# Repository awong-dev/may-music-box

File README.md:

# May Music Box

This is a little project I made for my daughter. It's an
mp3 player that reads off an SD-card that's built to
replace the guts of a Munchkin Mozart Music Cube.

Why do this? Cause electronic beepy toys for toddlers
are sooo much better if you can control what gets played
on them. :)

## Features
  * Super low power draw. Inactive, draws around 210uA. Active ~50-60mA. With a 1200mAH battery, that's ~8 months of sleep (not really since the battery will leak), or 20 hours of play on one charge.
  * Hardware button debounce. Cuz I could.
  * LEDs that act ike Peak-meter to give your toddler the authentic club feel.
  * Way too much love and sweat put into buliding this thing.
  * The word "mayberry" is printed on the PCB. :)

## What's in this repository
  * Arduino sketch for the MCU that handles the input buttons and playback.
  * vdsp4 assembly code for handling mono downmix, and LED pulsing in of the VS1053b chip
  * Eagle files for the contol PCB.

## Quirks
  * There is a fork of the Adafruit vs1053b library. The mainline library has (multiple) synchronization bugs that lead to corrupted state. This fork fixes the major ones. Remove once upstream merges the fixes.

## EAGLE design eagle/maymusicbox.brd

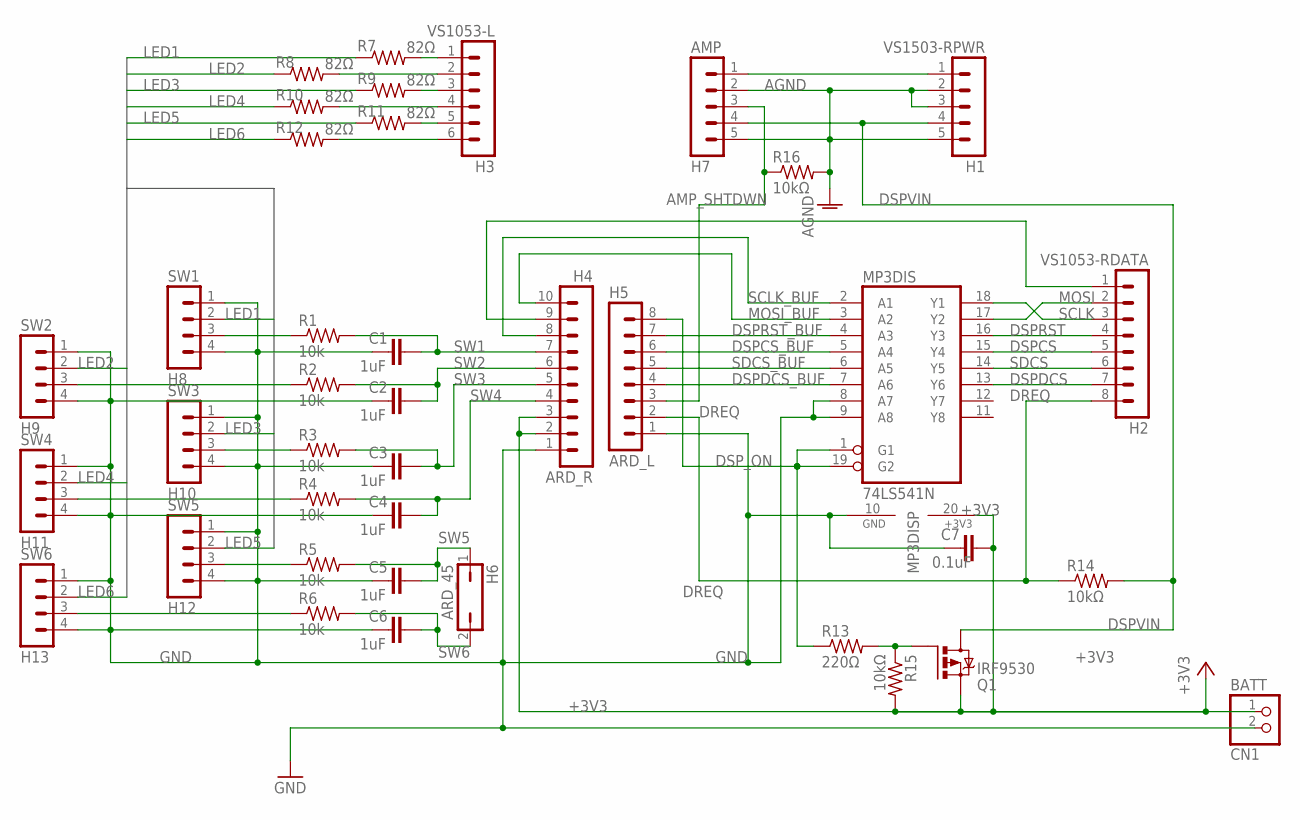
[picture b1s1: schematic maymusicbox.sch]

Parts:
C1, C2, C3, C4, C5, C6: 1uF; C025-025X050
C7: 0.1uF; C025-025X050
CN1: BATT; JST-PH-2-THM
H1: VS1503-RPWR; MA05-1
H2: VS1053-RDATA; MA08-1
H3: VS1053-L; MA06-1
H4: ARD_R; MA10-1
H5: ARD_L; MA08-1
H6: ARD_45; JP1
H7: AMP; MA05-1
H8: SW1; MA04-1
H9: SW2; MA04-1
H10: SW3; MA04-1
H11: SW4; MA04-1
H12: SW5; MA04-1
H13: SW6; MA04-1
MP3DIS: 74LS541N; DIL20
Q1: IRF9530; TO220BV
R1, R2, R3, R4, R5, R6: 10k; 0207/2V
R7, R8, R9, R10, R11, R12: 82Ω; 0207/2V
R13: 220Ω; 0207/2V
R14, R15, R16: 10kΩ; 0207/2V

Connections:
+3V3: C7.2, CN1.1 (2), H4.2, H4.3, MP3DIS.20 (+3V3), Q1.S, R15.2
A+: H1.1, H7.1
AGND: H1.2, H1.3, H1.5, H7.2, H7.5, R16.2
AMP_SHTDWN: H5.3, H7.3, R16.1
DREQ: H2.8, H5.2, R14.1
DSPCS: H2.5, MP3DIS.15 (Y4)
DSPCS_BUF: H5.6, MP3DIS.5 (A4)
DSPDCS: H2.7, MP3DIS.13 (Y6)
DSPDCS_BUF: H5.4, MP3DIS.7 (A6)
DSPRST: H2.4, MP3DIS.16 (Y3)
DSPRST_BUF: H5.7, MP3DIS.4 (A3)
DSPVIN: H1.4, H7.4, Q1.D, R14.2
DSP_ON: H5.8, MP3DIS.1 (G1), MP3DIS.19 (G2), R13.1
GND: C1.1, C2.1, C3.1, C4.1, C5.1, C6.1, C7.1, CN1.2 (1), H4.1, H5.1, H8.1, H8.4, H9.1, H9.4, H10.1, H10.4, H11.1, H11.4, H12.1, H12.4, H13.1, H13.4, MP3DIS.8 (A7), MP3DIS.9 (A8), MP3DIS.10 (GND)
LED1: H8.2, R7.1
LED2: H9.2, R8.1
LED3: H10.2, R9.1
LED4: H11.2, R10.1
LED5: H12.2, R11.1
LED6: H13.2, R12.1
MISO: H2.1, H4.9
MOSI: H2.2, MP3DIS.17 (Y2)
MOSI_BUF: H4.10, MP3DIS.3 (A2)
unnamed: H3.1, R7.2
unnamed: H3.2, R8.2
unnamed: Q1.G, R13.2, R15.1
unnamed: H3.3, R9.2
unnamed: H3.4, R10.2
unnamed: H3.5, R11.2
unnamed: H3.6, R12.2
unnamed: H10.3, R3.1
unnamed: H9.3, R2.1
unnamed: H8.3, R1.1
unnamed: H11.3, R4.1
unnamed: H12.3, R5.1
unnamed: H13.3, R6.1
SCLK: H2.3, MP3DIS.18 (Y1)
SCLK_BUF: H4.8, MP3DIS.2 (A1)
SDCS: H2.6, MP3DIS.14 (Y5)
SDCS_BUF: H5.5, MP3DIS.6 (A5)
SW1: C1.2, H4.7, R1.2
SW2: C2.2, H4.6, R2.2
SW3: C3.2, H4.5, R3.2
SW4: C4.2, H4.4, R4.2
SW5: C5.2, H6.1, R5.2
SW6: C6.2, H6.2, R6.2

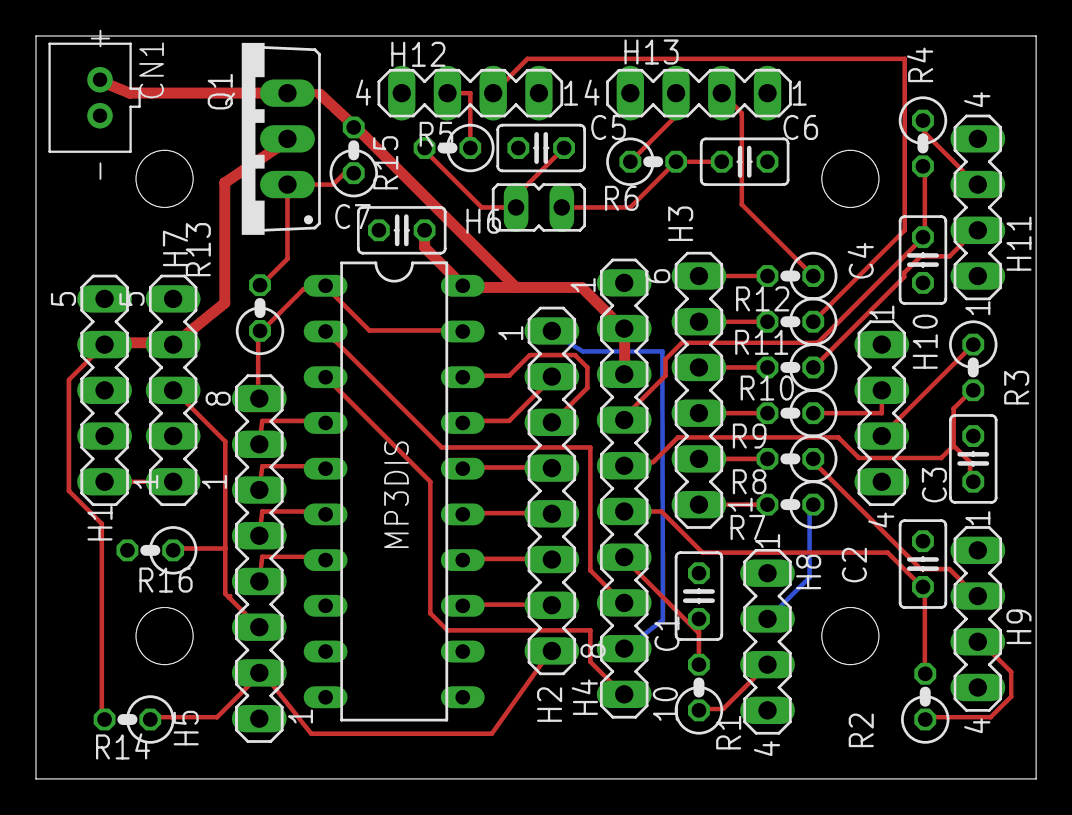
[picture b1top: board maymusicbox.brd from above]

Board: 2 copper layers, 55.6 x 41.3 mm, 39 parts (0 on the bottom side), 46 nets.

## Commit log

2017-04-10 Initial setup
2017-04-15 Fix the loops so they work. Ugh.
    Somehow I thought the delay slot held the operation that affected the
    jump. Of course, that makes no sense since the delay slot is the
    pipelined instruction that has already been fetched meaning the jump has
    already modified the PC for pre-fecth before it executes. This is what
    happens when you only code after the kid goes down. Grr.
2017-04-18 Music plays, but no gpio.
2017-04-18 Works with led flashing.
2017-04-19 Linear response
2017-04-19 squareroot response
2017-04-19 optimized a bit
2017-05-14 divide before squaring to avoid overflow
2017-05-14 Visually this looks sane now.
2017-05-24 Reasonable visual delay.
    Unfortuntly, the PWM frequency of 300hz means the sample is
    happening at 76800 Hz in the current code which is ludicrous.
    Sampling should happen at each PWM cycle edge instead. Change
    in next update.
2017-05-24 Simplified sample at 300hz
2017-05-24 Working basic peak meter
2017-05-24 Peak with degrade
2017-05-24 clean up code
2017-05-27 Just do a simple linear degrade
2017-05-27 Initial commit with project description
2017-05-27 Add arduino and eagle files.
2017-05-27 Fix readme
2018-01-08 Fix file naming
2018-02-12 Fix Schematic + Part to have 0 error issues
2018-04-23 Updated for V2 board, including pin wiring error
2023-04-07 Start rewriting May Music Box in esp-idf
2023-04-14 Building out most of the button control code.
2023-04-16 Break into proper header/impl files
2023-04-19 Most systems basically working
2023-04-19 Clean up button events to fire consistently.
2023-04-20 connect button to player
2023-04-20 LED pulse_active() start
2023-04-22 Most of led wire up done too now.
2023-04-22 Remove warnings
2023-04-22 Migrate from deprecated timer APIs
2023-04-23 Follow logic written
2023-04-24 Complete the LED acitons. There's something wrong with the timer_isr callback registration.
2023-04-24 Old-school gpio isr
2023-04-24 Go back to newer timer_isr registration. Still hangs on button-down.
2023-04-24 Move to single-channel per led
2023-04-30 Got at 300hz follow going!
2023-04-30 Tweak decay and brightness
2023-05-02 Add ULP button debounce program
2023-05-04 ULP Button histories now correct!
2023-05-06 Button fully in ULP
2023-05-08 All of it works but sleep now.
2023-05-08 Doesn't work and garbled
2023-05-10 Cleaned up a lot. Missing first button press
2023-05-10 Cleaner button interface
2023-05-11 Reuse first gpio sample.
2023-05-11 Separate out 'Stopped playing' sleep signal.
2023-05-12 cleanup Led class code
2023-05-12 Redo the led command logic
2023-05-15 Clean-up LED hold logic
2023-05-15 Fix Led ordering
2023-05-24 Get the wakeup semaphore working
2023-05-24 Clean-up button state publishing
2023-05-24 Correct sleep logic and poll
2023-08-06 Tweak led values to look pretty
2023-08-20 Plays continuously without sleeping and no crashes
2023-08-23 get sleeping count right
2023-09-11 It all works again
2023-11-22 Adjust volume
2023-11-22 Adjust brightness to max
2024-01-06 Add basic setup instrucitons for idf
2024-01-06 spell flute correctly
2024-04-28 Make it build on v5.2.1 idf and esp-adf master.
2025-03-02 Stably works again.
    Reenabled long fat filenames. (doh)
    Move the song seleciton out of the button scan to avoid multiple
    calls to start/stop when a button is pushed.
    Remove the call to time(nullptr) in wake_incr() which avoids an
    internal lock that would otherwise cause a deadlock if the interrupt
    handler executes while the audio playback is occurring. (double doh).
